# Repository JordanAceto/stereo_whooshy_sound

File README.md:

# Stereo Whooshy Sound

## This pedal accommodates various VCF plug-in boards and contains rich modulation features.
- The interface is loosely modeled after the Mu-Tron Bi-Phase with some additions.
- Flexible signal path configurations are possible, including true stereo, dual-mono, and series setups.

## [SCHEMATIC](https://github.com/JordanAceto/stereo_whooshy_sound/blob/master/hardware/main_pcb/construction_docs/stereo_whooshy_sound_schematic.pdf)

### Features:
- Guitar pedal style stomp box.
- Can accept a wide variety of [filter plug-in boards](https://github.com/JordanAceto/VCF_plug_in_boards).
- Manual frequency and resonance controls.
- Dual digitally generated LFO with morphing waveshaper, smoothly crossfades from triangle to sine to square to sample & hold.
- Analog envelope follower for when you want to quack and bwow instead of whoosh.
- CV/expression pedal inputs for each filter.

## Status of the project:

Task | Status |
---------|--------------|
Schematic capture | &#9745;
PCB layout | &#9745;
Test build | &#9745;
Safe to order boards| &#9744;

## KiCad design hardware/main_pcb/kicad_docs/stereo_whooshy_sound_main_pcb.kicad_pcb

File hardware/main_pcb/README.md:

# Main PCB

## The main PCB contains:
- input and output audio buffers
- software generated LFOs
- envelope followers
- two ports which accepts various VCF plug-in boards
- analog bypass switching
- power supply components
- designed to fit in a Hammond 1590XX enclosure

---

## [Schematic](https://github.com/JordanAceto/stereo_whooshy_sound/blob/master/hardware/main_pcb/construction_docs/stereo_whooshy_sound_schematic.pdf)

---

### PCB front view:

---

### PCB rear view:

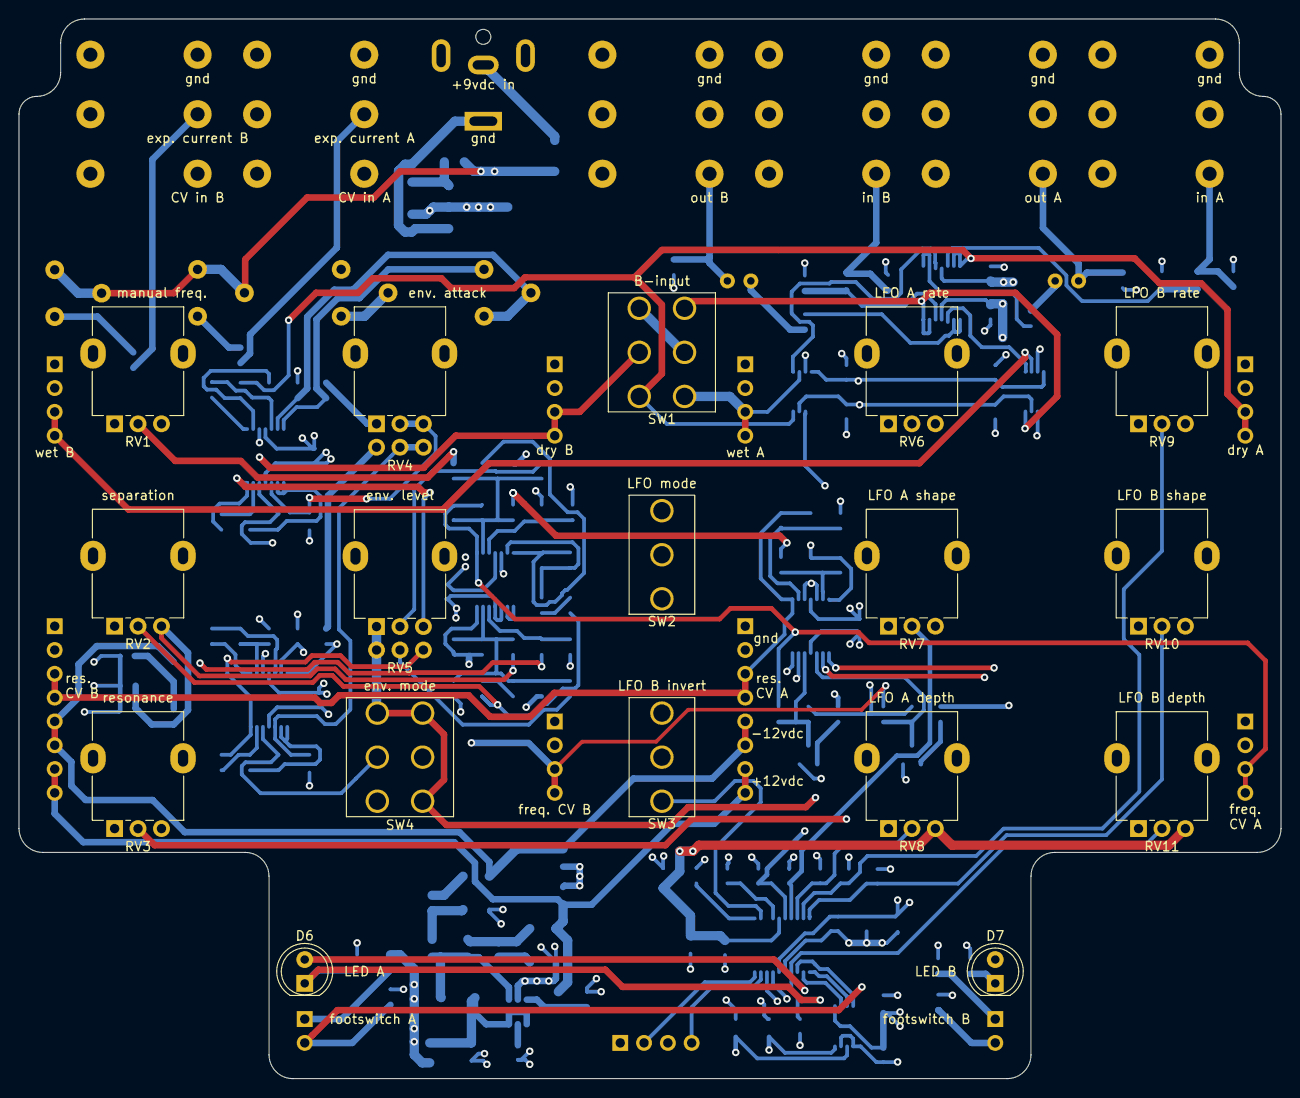
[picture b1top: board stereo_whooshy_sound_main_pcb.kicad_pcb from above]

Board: 4 copper layers, 134.6 x 113.0 mm, 178 parts (0 on the bottom side), 114 nets.

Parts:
C1, C2: 4n7; C_0805_2012Metric
C3, C9, C11, C13: 10u; C_0805_2012Metric
C4, C5, C6, C7, C8, C10, C12, C15, C17, C18, C20, C23, C27, C29, C30, C31, C32, C35, C36, C37, C38, C39, C40, C41, C46, C47: 100n; C_0603_1608Metric
C14, C19, C21, C42, C43: 1u; C_0805_2012Metric
C16, C22, C24: 4u7; C_0805_2012Metric
C25, C26: 10u bp; C_Radial_D6.3mm_H11.0mm_P2.50mm
C28, C33, C34: 22n; C_0603_1608Metric
C44, C45: 470n; C_0805_2012Metric
D1: B5819W; D_SOD-123
D2, D3, D4, D5: PMEG2010AEH; D_SOD-123F
D6, D7: LED; LED_D5.0mm
FB1, FB2, FB3, FB4: 100R @ 100MHz; L_0805_2012Metric
J1, J2, J3, J4, J5, J6: NRJ6HM-1; Jack_6.35mm_Neutrik_NRJ6HM-1_Horizontal
J7: signal_in_A; PinSocket_1x04_P2.54mm_Vertical
J8: signal_out_A; PinSocket_1x04_P2.54mm_Vertical
J9: freq_CV_in_A; PinSocket_1x04_P2.54mm_Vertical
J10: feedback_CV_and_PS_A; PinSocket_1x08_P2.54mm_Vertical
J11: signal_in_B; PinSocket_1x04_P2.54mm_Vertical
J12: signal_out_B; PinSocket_1x04_P2.54mm_Vertical
J13: freq_CV_in_B; PinSocket_1x04_P2.54mm_Vertical
J14: feedback_CV_and_PS_B; PinSocket_1x08_P2.54mm_Vertical
J15: swd_header; PinHeader_1x04_P2.54mm_Vertical
J16: Jack-DC; BarrelJack_CUI_PJ-063AH_Horizontal
J17: footswitch_A; PinHeader_1x02_P2.54mm_Vertical
J18: footswitch_B; PinHeader_1x02_P2.54mm_Vertical
L1: 10uH, 1.2A; L_Taiyo-Yuden_NR-50xx
Q1, Q2: MMBT3904; SOT-23
R1, R2, R3, R4: 2M2; R_0603_1608Metric
R5: 2k2; R_0603_1608Metric
R6, R7: 1R; R_0603_1608Metric
R8, R24, R34, R48, R49, R50, R62, R63, R64: 100k; R_0603_1608Metric
R9: 114k; R_0603_1608Metric
R10: 13k3; R_0603_1608Metric
R11, R43, R57: 20k; R_0603_1608Metric
R12, R13, R16, R17, R47, R61: 1k2; R_0603_1608Metric
R14, R15, R22, R23, R28, R42, R44, R51, R52, R58: 10k; R_0603_1608Metric
R18, R21, R26, R30, R31, R32, R37, R38, R39, R40, R41, R67, R68: 120k; R_0603_1608Metric
R19, R27, R56: 12k; R_0603_1608Metric
R20, R25, R29, R33, R35, R36, R55, R65, R66: 300k; R_0603_1608Metric
R45, R59: 30k; R_0603_1608Metric
R46, R60: 4k7; R_0603_1608Metric
R53, R54: 1M; R_0603_1608Metric
RV1, RV2, RV3, RV6, RV7, RV8, RV9, RV10, RV11: 10k; Potentiometer_Alpha_RD901F-40-00D_Single_Vertical
RV4: 500k_dual; Potentiometer_Alpha_RD902F-40-00D_Dual_Vertical
RV5: 10k_dual; Potentiometer_Alpha_RD902F-40-00D_Dual_Vertical
RV12, RV13, RV14, RV15: 100k trim; bourns_3306F
SW1: SW_DP_on_on_on; DPDT_mini_toggle
SW2: SW_SPDT_center_off; SPDT_mini_toggle
SW3: SW_SPDT; SPDT_mini_toggle
SW4: SW_DPDT_center_off; DPDT_mini_toggle
U1: TL074; TSSOP-14_4.4x5mm_P0.65mm
U2, U3, U4, U5: MCP6004; TSSOP-14_4.4x5mm_P0.65mm
U6, U7: DG469EQ; MSOP-8_3x3mm_P0.65mm
U8: STM32L031F4Px; TSSOP-20_4.4x6.5mm_P0.65mm
U9: MCP4822; TSSOP-8_3x3mm_P0.65mm
U10: LT1117-3.3; SOT-223-3_TabPin2
U11: LT3467A; TSOT-23-6
U12: LM4040DBZ-5; SOT-23

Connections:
+1V0: C23.1, R11.1, RV5.1, RV5.4, SW4.1, SW4.3, SW4.4, U5.7
+3.3VA: C14.1, C15.1, FB2.1, RV6.3, RV7.3, RV8.3, RV9.3, RV10.3, RV11.3, U8.5
+3V3: C3.1, C6.1, C7.1, C8.1, C9.1, C10.1, C12.1, C13.1, C46.1, C47.1, FB2.2, J15.1, R18.2, R39.2, U2.4, U3.4, U4.4, U5.4, U8.16, U9.1, U10.2
+9V: D1.1, FB1.2, FB3.2, R51.1, R52.1, RV12.1, RV12.2, RV13.1, RV13.2
+12V: C4.1, C24.1, C27.1, C30.1, D4.1, J10.7, J10.8, J14.7, J14.8, R9.2, U1.4, U6.4, U7.4
-5V: C20.2, R5.1, R8.2, R33.2, R66.2, RV1.3, RV2.3, RV3.3, U12.2
-12V: C5.2, C22.2, C29.2, C32.2, D5.2, FB4.1, J10.5, J10.6, J14.5, J14.6, U1.11, U6.7, U7.7
/VCF_plug_in_board_ports/feedback_CV_in_A: C28.1, J10.3, J10.4, J14.3, J14.4, R21.1, U5.1
/VCF_plug_in_board_ports/freq_CV_in_A: C33.1, J9.3, J9.4, R19.2, R40.1, U4.1
/VCF_plug_in_board_ports/freq_CV_in_B: C34.1, J13.3, J13.4, R41.1, R56.2, U4.14
/audio_input_buffers/dry_in_A: C1.2, J1.T, R1.1
/audio_input_buffers/dry_in_B: C2.2, J3.T, R3.1
/audio_output_buffers/audio_in_A: U1.3, U6.1
/audio_output_buffers/audio_in_B: U1.10, U7.1
/audio_output_buffers/final_out_A: C25.1, J2.T, R14.1
/audio_output_buffers/final_out_B: C26.1, J4.T, R15.1
/bypass_switches/bypass_logic_in_A: J17.2, R53.1, R67.2, U6.6
/bypass_switches/bypass_logic_in_B: J18.2, R54.1, R68.2, U7.6
/bypass_switches/wet_in_B: J12.3, J12.4, U7.2
/control_voltage_generators/cv_summers/env_A: R32.2, RV5.2
/control_voltage_generators/cv_summers/env_B: R38.2, RV5.5
/control_voltage_generators/cv_summers/lfo_A: C43.1, R31.2, U9.8
/control_voltage_generators/cv_summers/lfo_B: C42.1, R37.2, U9.6
/control_voltage_generators/cv_summers/manual_freq: R29.2, R35.2, RV1.2
/control_voltage_generators/cv_summers/separation_A: C31.1, R26.1, R30.2, U4.7
/control_voltage_generators/cv_summers/separation_B: R25.2, R36.2, RV2.2
/control_voltage_generators/exp_ped_ring_current_A: J5.R, R22.2
/control_voltage_generators/exp_ped_ring_current_B: J6.R, R23.2
/control_voltage_generators/ext_cv_A: J5.T, R34.2
/control_voltage_generators/ext_cv_B: J6.T, R24.2
/control_voltage_generators/lfo/lfo_1_depth_cv: C37.1, RV8.2, U8.8
/control_voltage_generators/lfo/lfo_1_rate_cv: C35.1, RV6.2, U8.6
/control_voltage_generators/lfo/lfo_1_shape_cv: C36.1, RV7.2, U8.7
/control_voltage_generators/lfo/lfo_2_depth_cv: C40.1, RV11.2, U8.14
/control_voltage_generators/lfo/lfo_2_rate_cv: C38.1, RV9.2, U8.9
/control_voltage_generators/lfo/lfo_2_shape_cv: C39.1, RV10.2, U8.10
/control_voltage_generators/lfo/lfo_inv_b_sw: SW3.3, U8.2
/control_voltage_generators/lfo/lfo_mode_sw_1: SW2.1, U8.17
/control_voltage_generators/lfo/lfo_mode_sw_2: SW2.3, U8.18
/control_voltage_generators/lfo/spi1_dac_cs: U8.12, U9.2
/control_voltage_generators/lfo/spi1_mosi: U8.13, U9.4
/control_voltage_generators/lfo/spi1_sck: U8.11, U9.3
/control_voltage_generators/lfo/sys_swclk: J15.2, U8.20
/control_voltage_generators/lfo/sys_swdio: J15.4, U8.19
/dry_A: J7.3, J7.4, R43.2, SW1.6, U1.6, U1.7, U6.8
/dry_B: SW1.1, U1.13, U1.14, U7.8
/power_supply/9VDC_in: D1.2, J16.2
/switched_dry_B: J11.3, J11.4, R57.2, SW1.5
/wet_A: J8.3, J8.4, SW1.3, U6.2
GND: C3.2, C4.2, C5.1, C6.2, C7.2, C8.2, C9.2, C10.2, C11.2, C12.2, C13.2, C14.2, C15.2, C16.2, C17.2, C18.1, C20.1, C22.1, C24.2, C27.2, C29.1, C30.2, C32.1, C35.2, C36.2, C37.2, C38.2, C39.2, C40.2, C41.2, C42.2, C43.2, C44.2, C45.2, C46.2, C47.2, D2.1, D3.2, J1.S, J1.TN, J2.S, J3.S, J3.TN, J4.S, J5.S, J5.TN, J6.S, J6.TN, J7.1, J7.2, J8.1, J8.2, J9.1, J9.2, J10.1, J10.2, J11.1, J11.2, J12.1, J12.2, J13.1, J13.2, J14.1, J14.2, J15.3, J16.1, Q1.2, Q2.2, R1.2, R2.2, R3.2, R4.2, R10.1, R14.2, R15.2, R16.2, R17.2, R27.2, R28.2, R42.2, R47.1, R53.2, R54.2, R61.1, RV1.1, RV2.1, RV3.1, RV6.1, RV7.1, RV8.1, RV9.1, RV10.1, RV11.1, SW2.2, SW3.2, U2.3, U2.11, U3.3, U3.11, U4.5, U4.10, U4.11, U5.3, U5.5, U5.11, U6.3, U7.3, U8.15, U9.5, U9.7, U10.1, U11.2, U12.1
unnamed: C1.1, R2.1, U1.5
unnamed: C2.1, R4.1, U1.12
unnamed: C11.1, FB1.1, U10.3
unnamed: C16.1, FB3.1, L1.1, U11.4, U11.6
unnamed: C17.1, U11.5
unnamed: C18.2, FB4.2, R5.2
unnamed: C19.1, C21.2, L1.2, U11.1
unnamed: C19.2, D2.2, R6.1
unnamed: C21.1, D4.2, R7.2
unnamed: C23.2, R8.1, R11.2, U5.6
unnamed: C25.2, R12.1
unnamed: C26.2, R13.1
unnamed: C28.2, R20.1, R21.2, U5.2
unnamed: C31.2, R26.2, R55.1, U4.6
unnamed: C33.2, R29.1, R30.1, R31.1, R32.1, R33.1, R40.2, U4.2
unnamed: C34.2, R35.1, R37.1, R38.1, R41.2, R65.1, R66.1, U4.13
unnamed: C41.1, U8.4
unnamed: C44.1, RV4.2, RV4.3, U2.10
unnamed: C45.1, RV4.5, RV4.6, U3.10
unnamed: D3.1, R7.1
unnamed: D5.1, R6.2
unnamed: D6.1, R16.1, U5.13
unnamed: D6.2, U5.14
unnamed: D7.1, R17.1, U5.9
unnamed: D7.2, U5.8
unnamed: J17.1, R51.2
unnamed: J18.1, R52.2
unnamed: Q1.1, R67.1
unnamed: Q1.3, R18.1, R19.1, U5.12
unnamed: Q2.1, R68.1
unnamed: Q2.3, R39.1, R56.1, U5.10
unnamed: R9.1, R10.2, U11.3
unnamed: R12.2, U1.1, U1.2
unnamed: R13.2, U1.8, U1.9
unnamed: R20.2, RV3.2
unnamed: R22.1, RV12.3
unnamed: R23.1, RV13.3
unnamed: R24.1, R27.1, U4.12
unnamed: R25.1, R55.2
unnamed: R28.1, R34.1, U4.3
unnamed: R36.1, R65.2
unnamed: R42.1, U8.1
unnamed: R43.1, R44.2, U2.2
unnamed: R44.1, R45.1, U2.5
unnamed: R45.2, U2.1
unnamed: R46.1, RV4.1
unnamed: R46.2, RV14.1, U2.7
unnamed: R47.2, RV14.2, RV14.3, U2.6
unnamed: R48.1, R50.2, U2.13
unnamed: R48.2, R49.2, U2.8, U2.9
unnamed: R49.1, SW4.2, U2.12
unnamed: R50.1, RV5.3, U2.14
unnamed: R57.1, R58.2, U3.2
unnamed: R58.1, R59.1, U3.5
unnamed: R59.2, U3.1
unnamed: R60.1, RV4.4
unnamed: R60.2, RV15.1, U3.7
unnamed: R61.2, RV15.2, RV15.3, U3.6
unnamed: R62.1, R64.2, U3.13
unnamed: R62.2, R63.2, U3.8, U3.9
unnamed: R63.1, SW4.5, U3.12
unnamed: R64.1, RV5.6, U3.14
unnamed: SW1.2, SW1.4
unnamed: U4.8, U4.9

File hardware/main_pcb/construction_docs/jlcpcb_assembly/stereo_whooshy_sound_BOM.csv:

Comment,Designator,Footprint,LCSC Part Number
MMBT3904,"Q1,Q2",SOT-23-3,C20526
12k,"R19,R56,R27",0603,C22790
120k,"R67,R18,R68,R39,R41,R40,R38,R37,R30,R32,R31,R26,R21",0603,C25808
DG469EQ,"U7,U6",MSOP-8_3x3.0x0.65P,C145215
MCP6004,"U5,U4,U3,U2",TSSOP-14_4.4x5_P0.65P,C50282
TL074,U1,TSSOP-14_4.4x5_P0.65P,C96507
300k,"R66,R65,R55,R36,R35,R33,R29,R25,R20",0603,C23024
10k,"R28,R58,R52,R51,R44,R42,R23,R22,R15,R14",0603,C25804
100k,"R24,R64,R63,R62,R50,R49,R48,R34,R8",0603,C25803
1M,"R54,R53",0603,C22935
100n,"C32,C30,C29,C27,C47,C46,C41,C40,C39,C38,C37,C36,C35,C31,C23,C20,C18,C17,C15,C12,C10,C8,C7,C6,C5,C4",0603,C14663
1k2,"R61,R47,R17,R16,R13,R12",0603,C22765
4k7,"R60,R46",0603,C23162
30k,"R59,R45",0603,C22984
20k,"R57,R43,R11",0603,C4184
470n,"C45,C44",0805,C13967
4n7,"C2,C1",0805,C1744
1R,"R7,R6",0603,C22936
2k2,R5,0603,C4190
2M2,"R4,R3,R2,R1",0603,C22938
100R @ 100MHz,"FB4,FB3,FB2,FB1",L_0805_2012Metric,C1015
B5819W,D1,D_SOD-123,C8598
1u,"C43,C42,C21,C19,C14",0805,C28323
22n,"C34,C33,C28",0603,C21122
4u7,"C24,C22,C16",0805,C1779
10u,"C13,C11,C9,C3",0805,C15850

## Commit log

2021-01-27 progress on schemo
2021-08-07 progress on pcb layout
2021-08-08 reduce analog switch count, tidy up
2021-08-08 add gitignore
2021-08-08 add firmware, ported from mono-whooshy-sound, needs work
2021-08-08 tidy up kicad docs
2021-08-08 add trimpot datasheet
2021-08-08 generate interactive BOM
2021-08-08 generate jlcpcb assembly docs
2021-08-08 tidy up
2021-08-08 generate gerbers
2021-08-08 remove warnings from schematic pdf
2021-12-25 add pics
2021-12-25 add front panel
2022-01-16 add early pics, update readme
2022-05-17 Fix prob with MODER constant, enable port B and C
2022-05-17 Add missing param to docstring
2022-05-18 Fix startup/makefile bug that messed with C++ constructors
2022-05-18 Minor ADC name changes
2022-05-18 Change GPIO initialization, add get GPIO pin function
2022-05-18 Small int type changes to DAC module
2022-05-18 Add debounced switch module
2022-05-18 Add UI controls module
2022-05-18 Fix import bug in UI controls
2022-05-18 Update main, basic app now working
2022-05-18 Fix bug with LFO random wave, minor LFO changes
2022-07-31 Add some pics of finished pedal, update README
2022-07-31 Update hardware README
2022-07-31 Update front panel, now KiCad 6, tweak graphics
2022-07-31 Add jack panel documents
2022-07-31 Add licence text

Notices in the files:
hardware/main_pcb/kicad_docs/stereo_whooshy_sound_main_pcb.kicad_pcb:
License: CC by 4.0
